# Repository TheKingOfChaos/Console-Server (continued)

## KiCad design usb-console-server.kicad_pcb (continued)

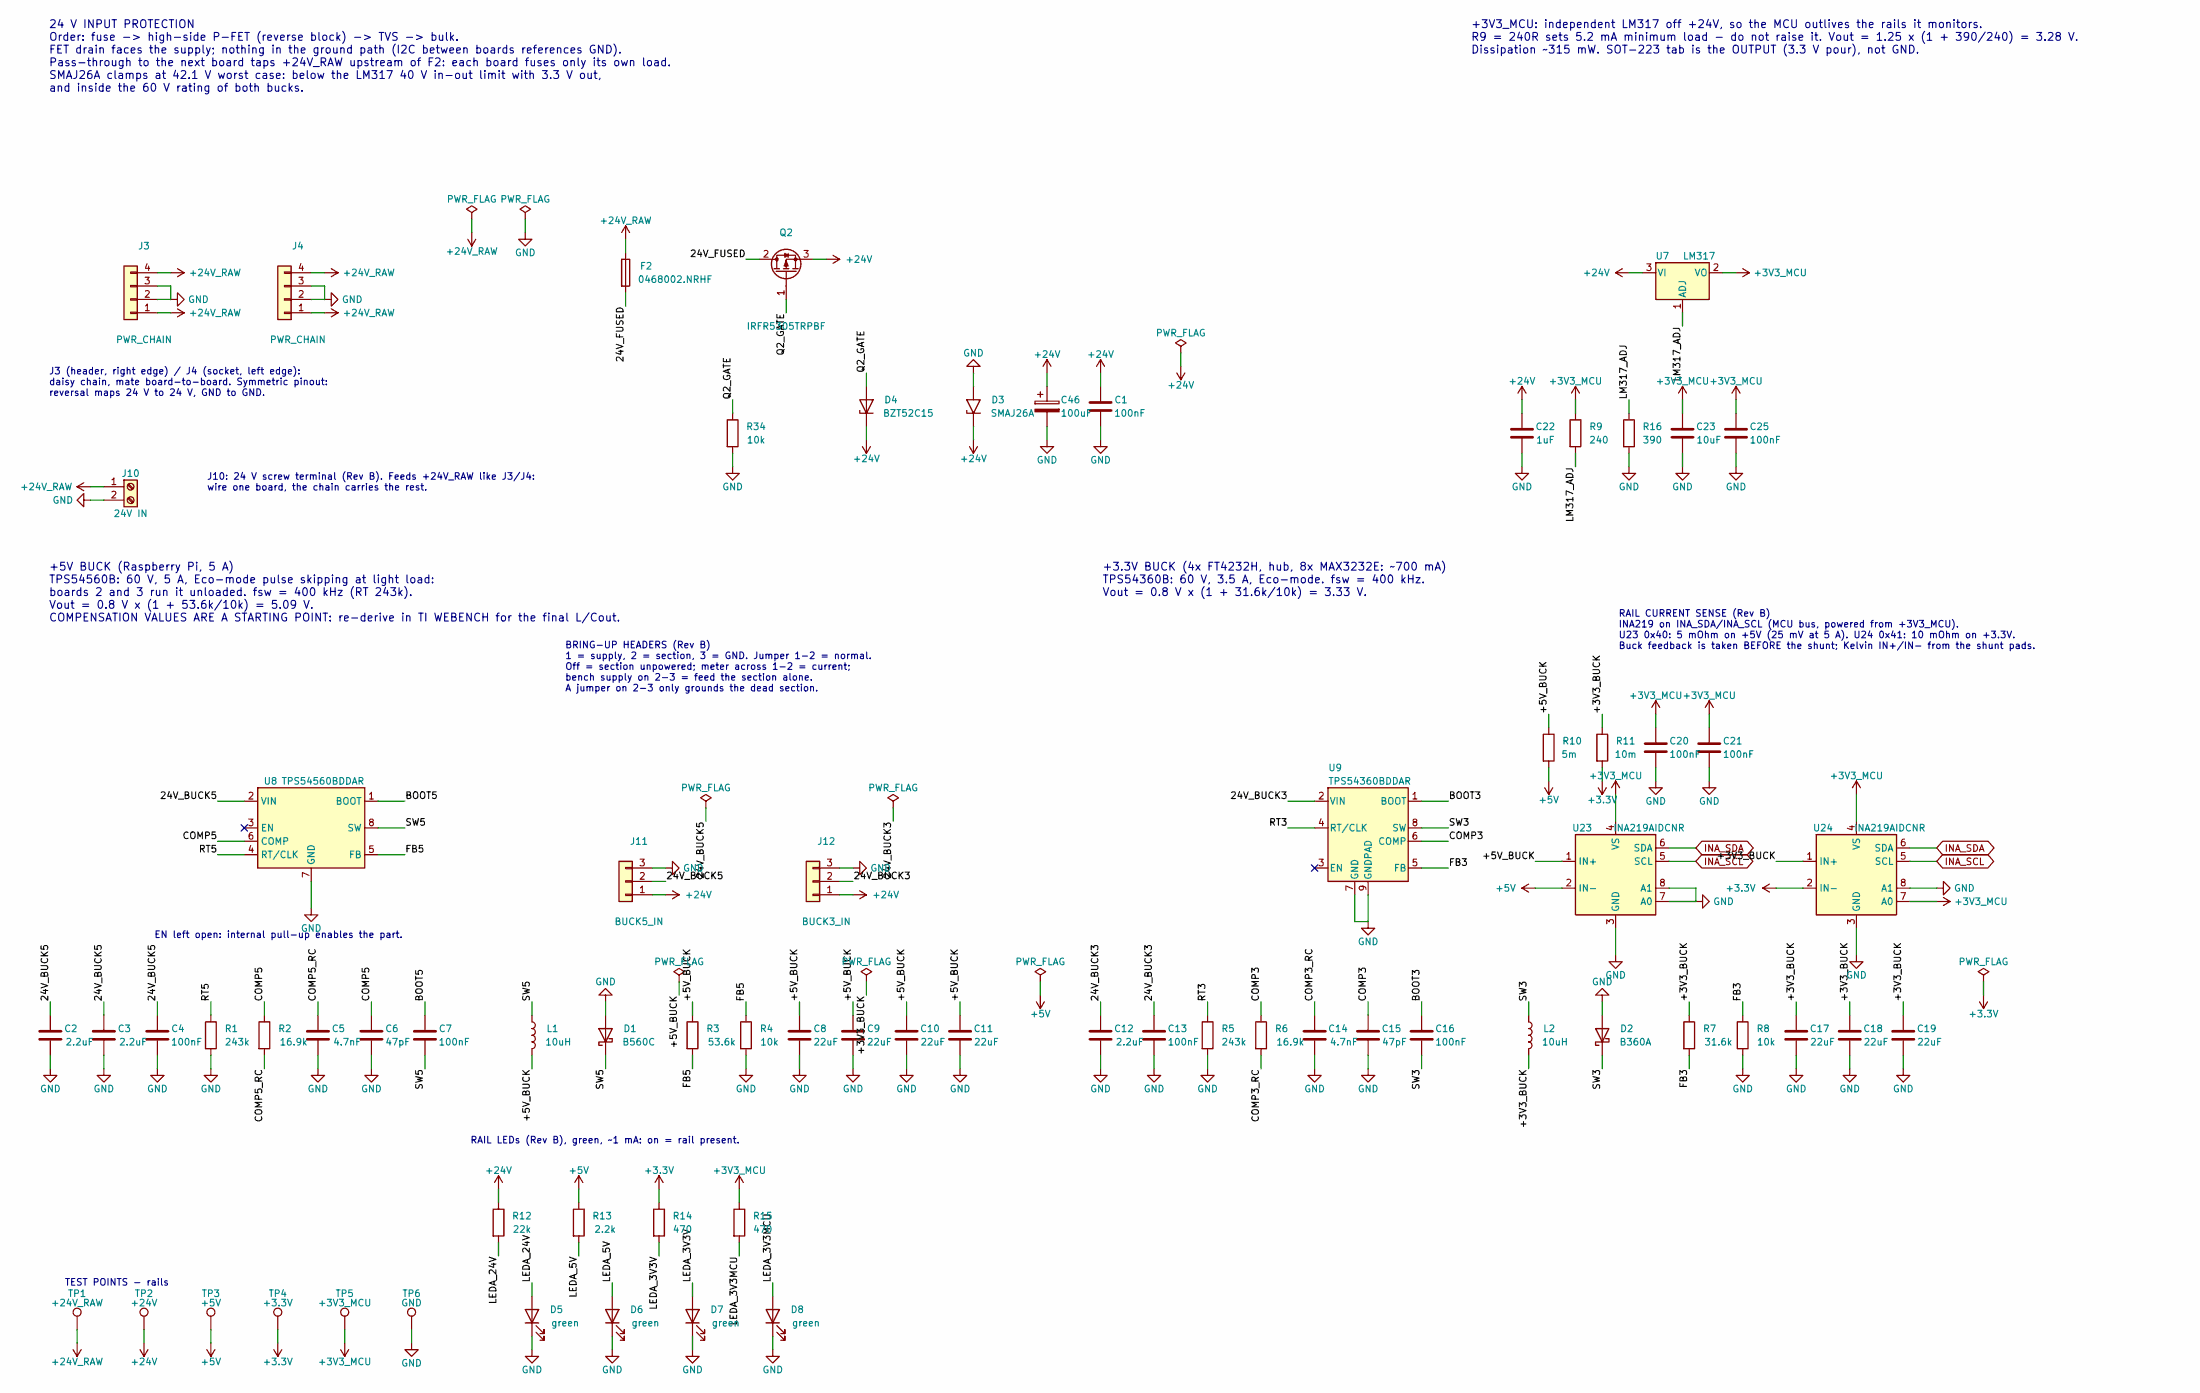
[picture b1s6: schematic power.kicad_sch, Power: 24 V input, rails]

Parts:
C1, C4, C7, C13, C16, C20, C21, C25: 100nF; C_0603_1608Metric; LCSC C14663
C2, C3, C12: 2.2uF; C_1210_3225Metric; LCSC C153036
C5, C14: 4.7nF; C_0603_1608Metric; LCSC C53987
C6, C15: 47pF; C_0603_1608Metric; LCSC C1671
C8, C9, C10, C11, C17, C18, C19: 22uF; C_1206_3216Metric; LCSC C77091
C22: 1uF; C_0805_2012Metric; LCSC C91185
C23: 10uF; C_0805_2012Metric; LCSC C15850
C46: 100uF; CP_Elec_10x10.5; LCSC C51953411
D1: B560C; D_SMC; LCSC C85100
D2: B360A; D_SMA; LCSC C94193
D3: SMAJ26A; D_SMA; LCSC C148225
D4: BZT52C15; D_SOD-123; LCSC C668893
D5, D6, D7, D8: green; LED_0603_1608Metric; LCSC C965805
F2: 0468002.NRHF; Fuse_1206_3216Metric; LCSC C187611
J3: PWR_CHAIN; PinHeader_1x04_P2.54mm_Horizontal; LCSC C492412
J4: PWR_CHAIN; PinSocket_1x04_P2.54mm_Horizontal; LCSC C2897386
J10: 24V IN; TerminalBlock_Phoenix_MKDS-1,5-2-5.08_1x02_P5.08mm_Horizont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; LCSC C8465
J11: BUCK5_IN; PinHeader_1x03_P2.54mm_Vertical; LCSC C49257
J12: BUCK3_IN; PinHeader_1x03_P2.54mm_Vertical; LCSC C49257
L1: 10uH; L_Bourns_SRP1265A; MPN TMPC1265HP-100MG-D; LCSC C305223
L2: 10uH; L_Bourns_SRP7028A_7.3x6.6mm; MPN SRP7028A-100M; LCSC C2687402
Q2: IRFR5305TRPBF; TO-252-3_L6.5-W6.1-P4.58-LS9.9-BR; LCSC C2624
R1, R5: 243k; R_0603_1608Metric; LCSC C403098
R2, R6: 16.9k; R_0603_1608Metric; LCSC C2933158
R3: 53.6k; R_0603_1608Metric; LCSC C2930115
R4, R8, R34: 10k; R_0603_1608Metric; LCSC C25804
R7: 31.6k; R_0603_1608Metric; LCSC C25967
R9: 240; R_0603_1608Metric; LCSC C114613
R10: 5m; R_2512_6332Metric; LCSC C393074
R11: 10m; R_1206_3216Metric; LCSC C188070
R12: 22k; R_0603_1608Metric; LCSC C31850
R13: 2.2k; R_0603_1608Metric; LCSC C4190
R14, R15: 470; R_0603_1608Metric; LCSC C23179
R16: 390; R_0603_1608Metric; LCSC C23151
TP1: +24V_RAW; TestPoint_Pad_D1.5mm
TP2: +24V; TestPoint_Pad_D1.5mm
TP3: +5V; TestPoint_Pad_D1.5mm
TP4: +3.3V; TestPoint_Pad_D1.5mm
TP5: +3V3_MCU; TestPoint_Pad_D1.5mm
TP6: GND; TestPoint_Pad_D1.5mm
U7: LM317; SOT-223-3_TabPin2; LCSC C5296732
U8: TPS54560BDDAR; Texas_HSOP-8-1EP_3.9x4.9mm_P1.27mm_ThermalVias; LCSC C1850354
U9: TPS54360BDDAR; TI_SO-PowerPAD-8_ThermalVias; LCSC C524806
U23, U24: INA219AIDCNR; SOT-23-8; LCSC C87469

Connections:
+3.3V: R11.2, R14.1, TP4.1, U24.2 (IN-); also elsewhere on the board
+3V3_MCU: C20.1, C21.1, C23.1, C25.1, R9.1, R15.1, TP5.1, U7.2 (VO), U23.4 (VS), U24.4 (VS), U24.7 (A0); also elsewhere on the board
+5V: R10.2, R13.1, TP3.1, U23.2 (IN-); also elsewhere on the board
+24V: C1.1, C22.1, C46.1, D3.1 (A1), D4.1 (K), J11.1, J12.1, Q2.3 (S), R12.1, TP2.1, U7.3 (VI); also elsewhere on the board
+24V_RAW: F2.1, J3.1, J3.4, J4.1, J4.4, J10.1, TP1.1
/Power/24V_BUCK3: C12.1, C13.1, J12.2, U9.2 (VIN)
/Power/24V_BUCK5: C2.1, C3.1, C4.1, J11.2, U8.2 (VIN)
/Power/24V_FUSED: F2.2, Q2.2 (D)
/Power/+3V3_BUCK: C17.1, C18.1, C19.1, L2.2, R7.1, R11.1, U24.1 (IN+)
/Power/+5V_BUCK: C8.1, C9.1, C10.1, C11.1, L1.2, R3.1, R10.1, U23.1 (IN+)
/Power/BOOT3: C16.1, U9.1 (BOOT)
/Power/BOOT5: C7.1, U8.1 (BOOT)
/Power/COMP3: C15.1, R6.1, U9.6 (COMP)
/Power/COMP3_RC: C14.1, R6.2
/Power/COMP5: C6.1, R2.1, U8.6 (COMP)
/Power/COMP5_RC: C5.1, R2.2
/Power/FB3: R7.2, R8.1, U9.5 (FB)
/Power/FB5: R3.2, R4.1, U8.5 (FB)
/Power/LEDA_3V3MCU: D8.2 (A), R15.2
/Power/LEDA_3V3V: D7.2 (A), R14.2
/Power/LEDA_5V: D6.2 (A), R13.2
/Power/LEDA_24V: D5.2 (A), R12.2
/Power/LM317_ADJ: R9.2, R16.1, U7.1 (ADJ)
/Power/Q2_GATE: D4.2 (A), Q2.1 (G), R34.1
/Power/RT3: R5.1, U9.4 (RT/CLK)
/Power/RT5: R1.1, U8.4 (RT/CLK)
/Power/SW3: C16.2, D2.1 (K), L2.1, U9.8 (SW)
/Power/SW5: C7.2, D1.1 (K), L1.1, U8.8 (SW)
GND: C1.2, C2.2, C3.2, C4.2, C5.2, C6.2, C8.2, C9.2, C10.2, C11.2, C12.2, C13.2, C14.2, C15.2, C17.2, C18.2, C19.2, C20.2, C21.2, C22.2, C23.2, C25.2, C46.2, D1.2 (A), D2.2 (A), D3.2 (A2), D5.1 (K), D6.1 (K), D7.1 (K), D8.1 (K), J3.2, J3.3, J4.2, J4.3, J10.2, J11.3, J12.3, R1.2, R4.2, R5.2, R8.2, R16.2, R34.2, TP6.1, U8.7 (GND), U8.9 (GND), U9.7 (GND), U9.9 (GNDPAD), U23.3 (GND), U23.7 (A0), U23.8 (A1), U24.3 (GND), U24.8 (A1); also elsewhere on the board
INA_SCL: U23.5 (SCL), U24.5 (SCL); also elsewhere on the board
INA_SDA: U23.6 (SDA), U24.6 (SDA); also elsewhere on the board

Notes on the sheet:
TEST POINTS - rails
RAIL LEDs (Rev B), green, ~1 mA: on = rail present.
24 V INPUT PROTECTION Order: fuse -> high-side P-FET (reverse block) -> TVS -> bulk. FET drain faces the supply; nothing in the ground path (I2C between boards references GND). Pass-through to the next board taps +24V_RAW upstream of F2: each board fuses only its own load. SMAJ26A clamps at 42.1 V 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
EN left open: internal pull-up enables the part.
J10: 24 V screw terminal (Rev B). Feeds +24V_RAW like J3/J4: wire one board, the chain carries the rest.
RAIL CURRENT SENSE (Rev B) INA219 on INA_SDA/INA_SCL (MCU bus, powered from +3V3_MCU). U23 0x40: 5 mOhm on +5V (25 mV at 5 A). U24 0x41: 10 mOhm on +3.3V. Buck feedback is taken BEFORE the shunt; Kelvin IN+/IN- from the shunt pads.
J3 (header, right edge) / J4 (socket, left edge): daisy chain, mate board-to-board. Symmetric pinout: reversal maps 24 V to 24 V, GND to GND.
BRING-UP HEADERS (Rev B) 1 = supply, 2 = section, 3 = GND. Jumper 1-2 = normal. Off = section unpowered; meter across 1-2 = current; bench supply on 2-3 = feed the section alone. A jumper on 2-3 only grounds the dead section.
+3.3V BUCK (4x FT4232H, hub, 8x MAX3232E: ~700 mA) TPS54360B: 60 V, 3.5 A, Eco-mode. fsw = 400 kHz. Vout = 0.8 V x (1 + 31.6k/10k) = 3.33 V.
+3V3_MCU: independent LM317 off +24V, so the MCU outlives the rails it monitors. R9 = 240R sets 5.2 mA minimum load - do not raise it. Vout = 1.25 x (1 + 390/240) = 3.28 V. Dissipation ~315 mW. SOT-223 tab is the OUTPUT (3.3 V pour), not GND.
+5V BUCK (Raspberry Pi, 5 A) TPS54560B: 60 V, 5 A, Eco-mode pulse skipping at light load: boards 2 and 3 run it unloaded. fsw = 400 kHz (RT 243k). Vout = 0.8 V x (1 + 53.6k/10k) = 5.09 V. COMPENSATION VALUES ARE A STARTING POINT: re-derive in TI WEBENCH for the final L/Cout.

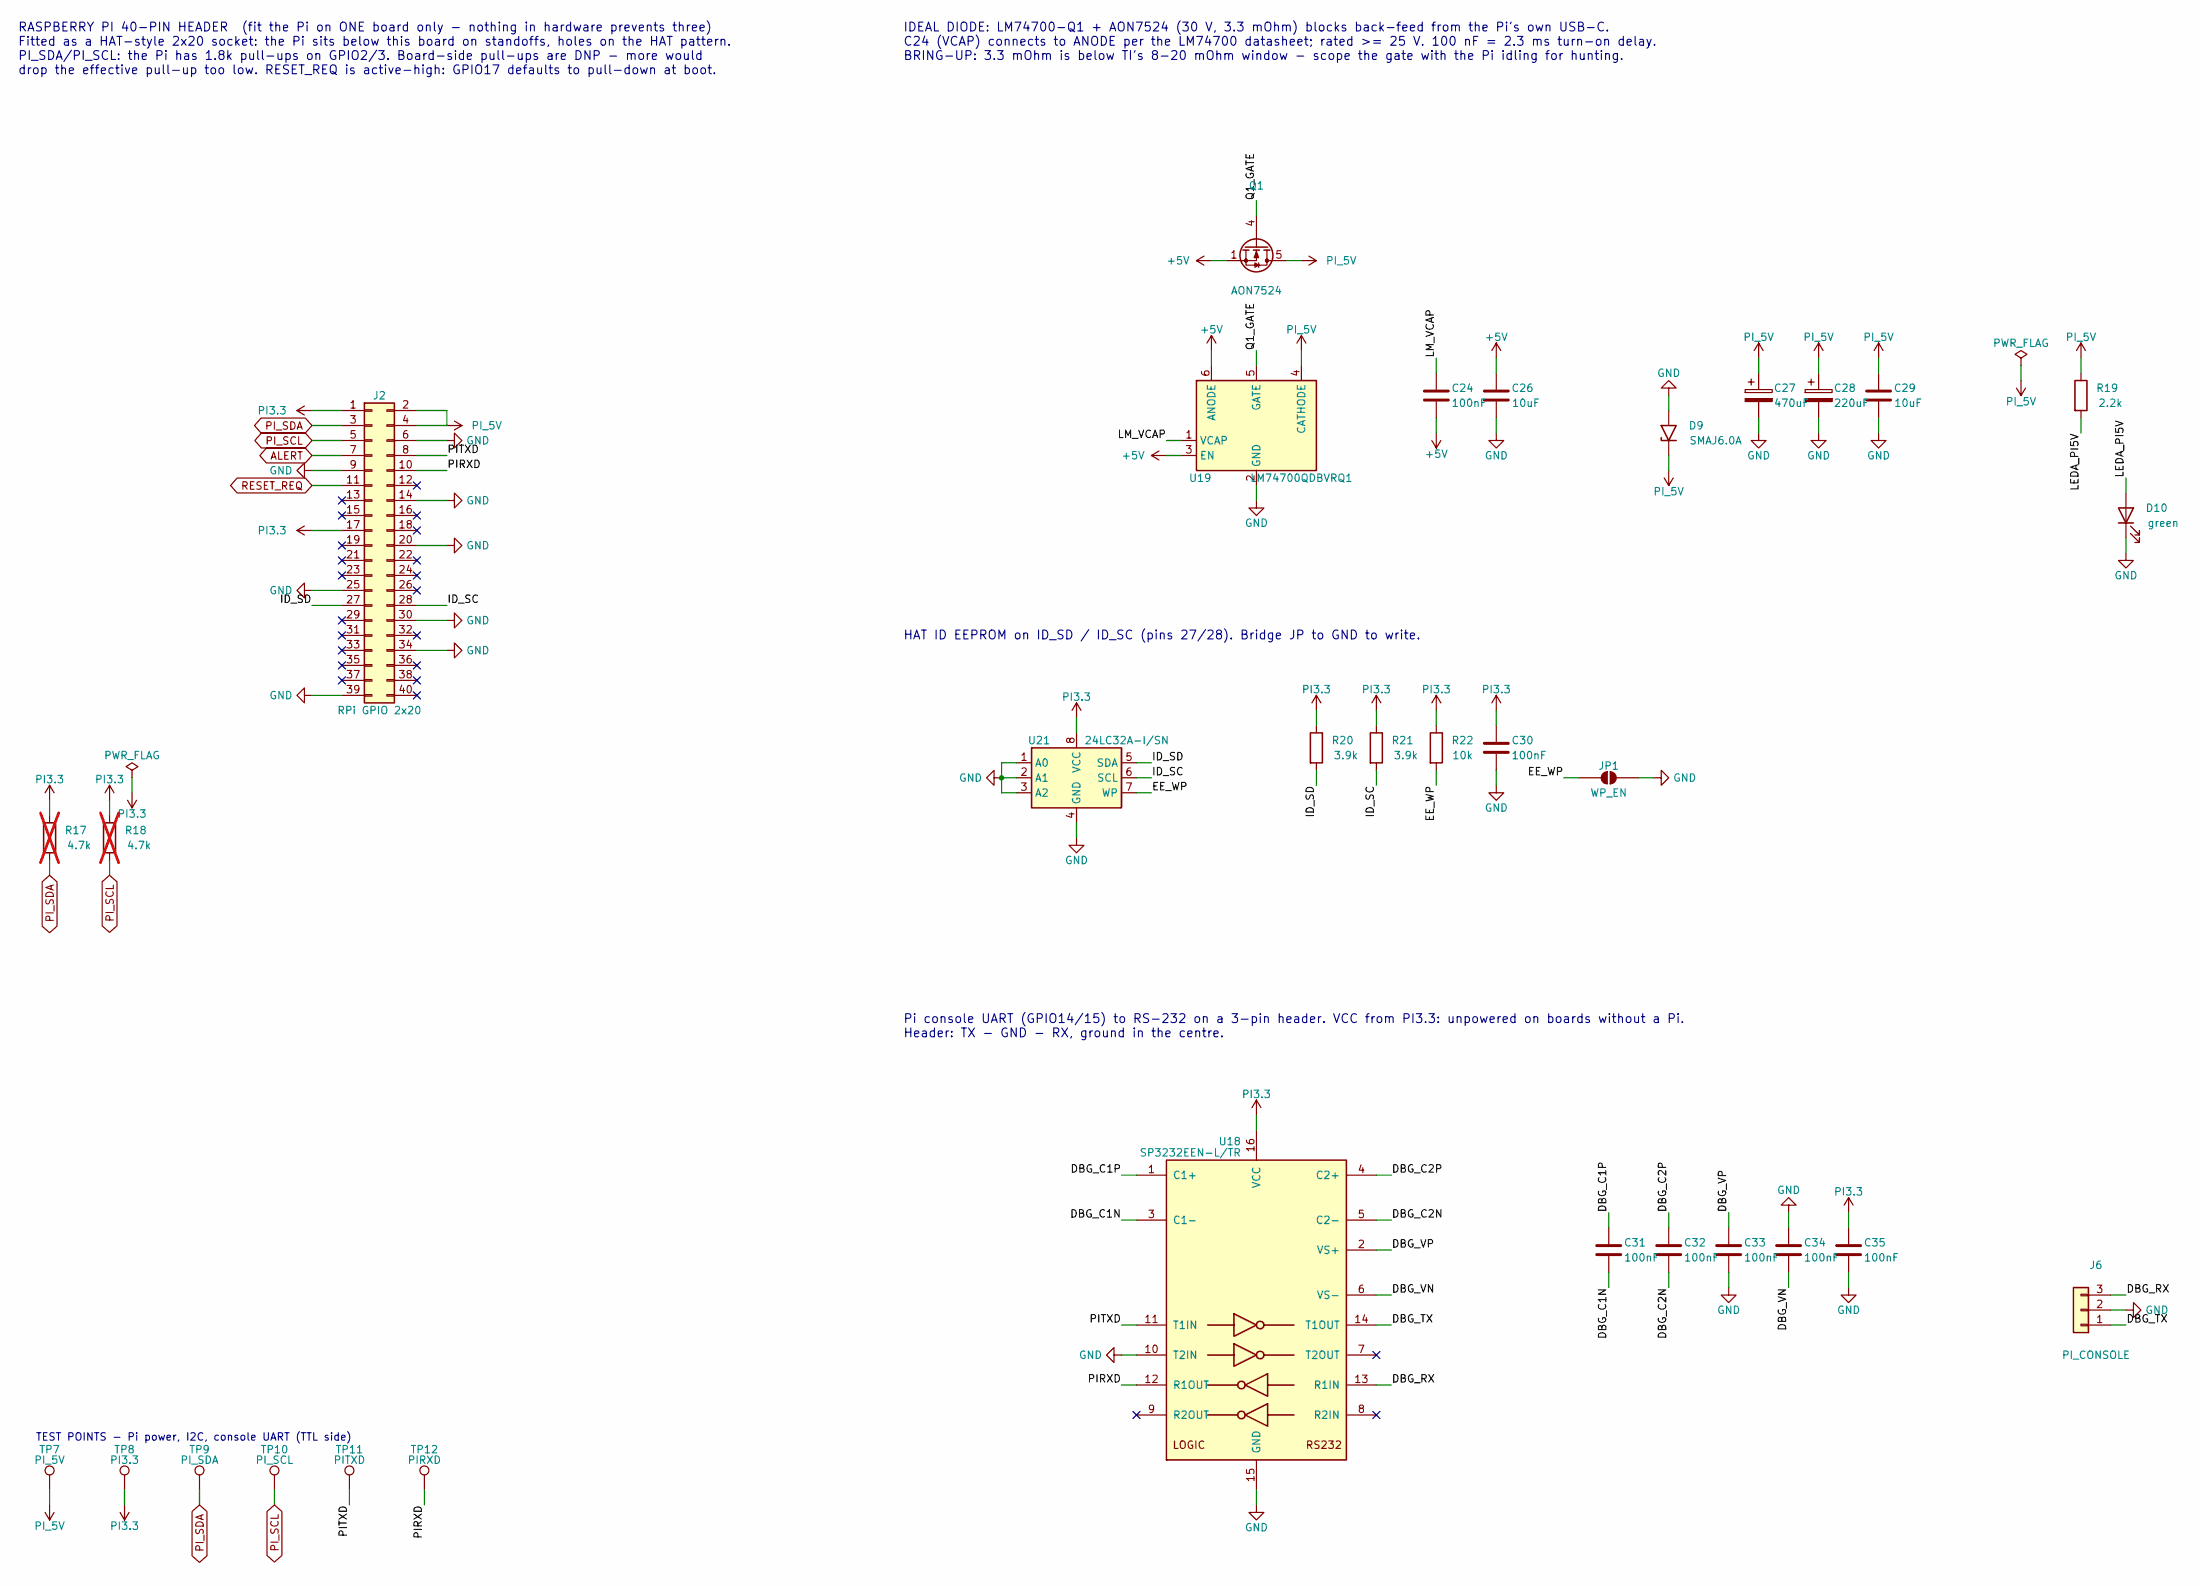
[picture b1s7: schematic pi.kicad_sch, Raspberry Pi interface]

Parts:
C24, C30, C31, C32, C33, C34, C35: 100nF; C_0603_1608Metric; LCSC C14663
C26, C29: 10uF; C_0805_2012Metric; LCSC C15850
C27: 470uF; CP_Elec_6.3x7.7; LCSC C335982
C28: 220uF; CP_Elec_6.3x5.4; LCSC C72494
D9: SMAJ6.0A; D_SMA; LCSC C223993
D10: green; LED_0603_1608Metric; LCSC C965805
J2: RPi GPIO 2x20; PinSocket_2x20_P2.54mm_Vertical; LCSC C2977589
J6: PI_CONSOLE; PinHeader_1x03_P2.54mm_Vertical; LCSC C49257
JP1: WP_EN; SolderJumper-2_P1.3mm_Open_RoundedPad1.0x1.5mm
Q1: AON7524; DFN-8_L3.0-W3.0-P0.65-BL-2; LCSC C431195
R17, R18: 4.7k; R_0603_1608Metric; LCSC C23162; not fitted
R19: 2.2k; R_0603_1608Metric; LCSC C4190
R20, R21: 3.9k; R_0603_1608Metric; LCSC C23018
R22: 10k; R_0603_1608Metric; LCSC C25804
TP7: PI_5V; TestPoint_Pad_D1.5mm
TP8: PI3.3; TestPoint_Pad_D1.5mm
TP9: PI_SDA; TestPoint_Pad_D1.0mm
TP10: PI_SCL; TestPoint_Pad_D1.0mm
TP11: PITXD; TestPoint_Pad_D1.0mm
TP12: PIRXD; TestPoint_Pad_D1.0mm
U18: SP3232EEN-L/TR; SOIC-16_3.9x9.9mm_P1.27mm; LCSC C9378
U19: LM74700QDBVRQ1; SOT-23-6; LCSC C2941042
U21: 24LC32A-I/SN; SOIC-8_3.9x4.9mm_P1.27mm; LCSC C511262

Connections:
+5V: C24.2, C26.1, Q1.1 (S), Q1.2 (S), Q1.3 (S), U19.3 (EN), U19.6 (ANODE); also elsewhere on the board
/Pi/DBG_C1N: C31.2, U18.3 (C1-)
/Pi/DBG_C1P: C31.1, U18.1 (C1+)
/Pi/DBG_C2N: C32.2, U18.5 (C2-)
/Pi/DBG_C2P: C32.1, U18.4 (C2+)
/Pi/DBG_RX: J6.3, U18.13 (R1IN)
/Pi/DBG_TX: J6.1, U18.14 (T1OUT)
/Pi/DBG_VN: C34.2, U18.6 (VS-)
/Pi/DBG_VP: C33.1, U18.2 (VS+)
/Pi/EE_WP: JP1.1 (A), R22.2, U21.7 (WP)
/Pi/ID_SC: J2.28, R21.2, U21.6 (SCL)
/Pi/ID_SD: J2.27, R20.2, U21.5 (SDA)
/Pi/LEDA_PI5V: D10.2 (A), R19.2
/Pi/LM_VCAP: C24.1, U19.1 (VCAP)
/Pi/PIRXD: J2.10, TP12.1, U18.12 (R1OUT)
/Pi/PITXD: J2.8, TP11.1, U18.11 (T1IN)
/Pi/Q1_GATE: Q1.4 (G), U19.5 (GATE)
ALERT: J2.7; also elsewhere on the board
GND: C26.2, C27.2, C28.2, C29.2, C30.2, C33.2, C34.1, C35.2, D9.2 (A2), D10.1 (K), J2.6, J2.9, J2.14, J2.20, J2.25, J2.30, J2.34, J2.39, J6.2, JP1.2 (B), U18.10 (T2IN), U18.15 (GND), U19.2 (GND), U21.1 (A0), U21.2 (A1), U21.3 (A2), U21.4 (GND); also elsewhere on the board
PI3.3: C30.1, C35.1, J2.1, J2.17, R17.1, R18.1, R20.1, R21.1, R22.1, TP8.1, U18.16 (VCC), U21.8 (VCC); also elsewhere on the board
PI_5V: C27.1, C28.1, C29.1, D9.1 (A1), J2.2, J2.4, Q1.5 (D), Q1.6 (D), Q1.7 (D), Q1.8 (D), Q1.9 (D), R19.1, TP7.1, U19.4 (CATHODE)
PI_SCL: J2.5, R18.2, TP10.1; also elsewhere on the board
PI_SDA: J2.3, R17.2, TP9.1; also elsewhere on the board
RESET_REQ: J2.11; also elsewhere on the board

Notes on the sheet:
Pi console UART (GPIO14/15) to RS-232 on a 3-pin header. VCC from PI3.3: unpowered on boards without a Pi. Header: TX - GND - RX, ground in the centre.
IDEAL DIODE: LM74700-Q1 + AON7524 (30 V, 3.3 mOhm) blocks back-feed from the Pi's own USB-C. C24 (VCAP) connects to ANODE per the LM74700 datasheet; rated >= 25 V. 100 nF = 2.3 ms turn-on delay. BRING-UP: 3.3 mOhm is below TI's 8-20 mOhm window - scope the gate with the Pi idling for hunting.
RASPBERRY PI 40-PIN HEADER (fit the Pi on ONE board only - nothing in hardware prevents three) Fitted as a HAT-style 2x20 socket: the Pi sits below this board on standoffs, holes on the HAT pattern. PI_SDA/PI_SCL: the Pi has 1.8k pull-ups on GPIO2/3. Board-side pull-ups are DNP - more would drop th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
TEST POINTS - Pi power, I2C, console UART (TTL side)
HAT ID EEPROM on ID_SD / ID_SC (pins 27/28). Bridge JP to GND to write.

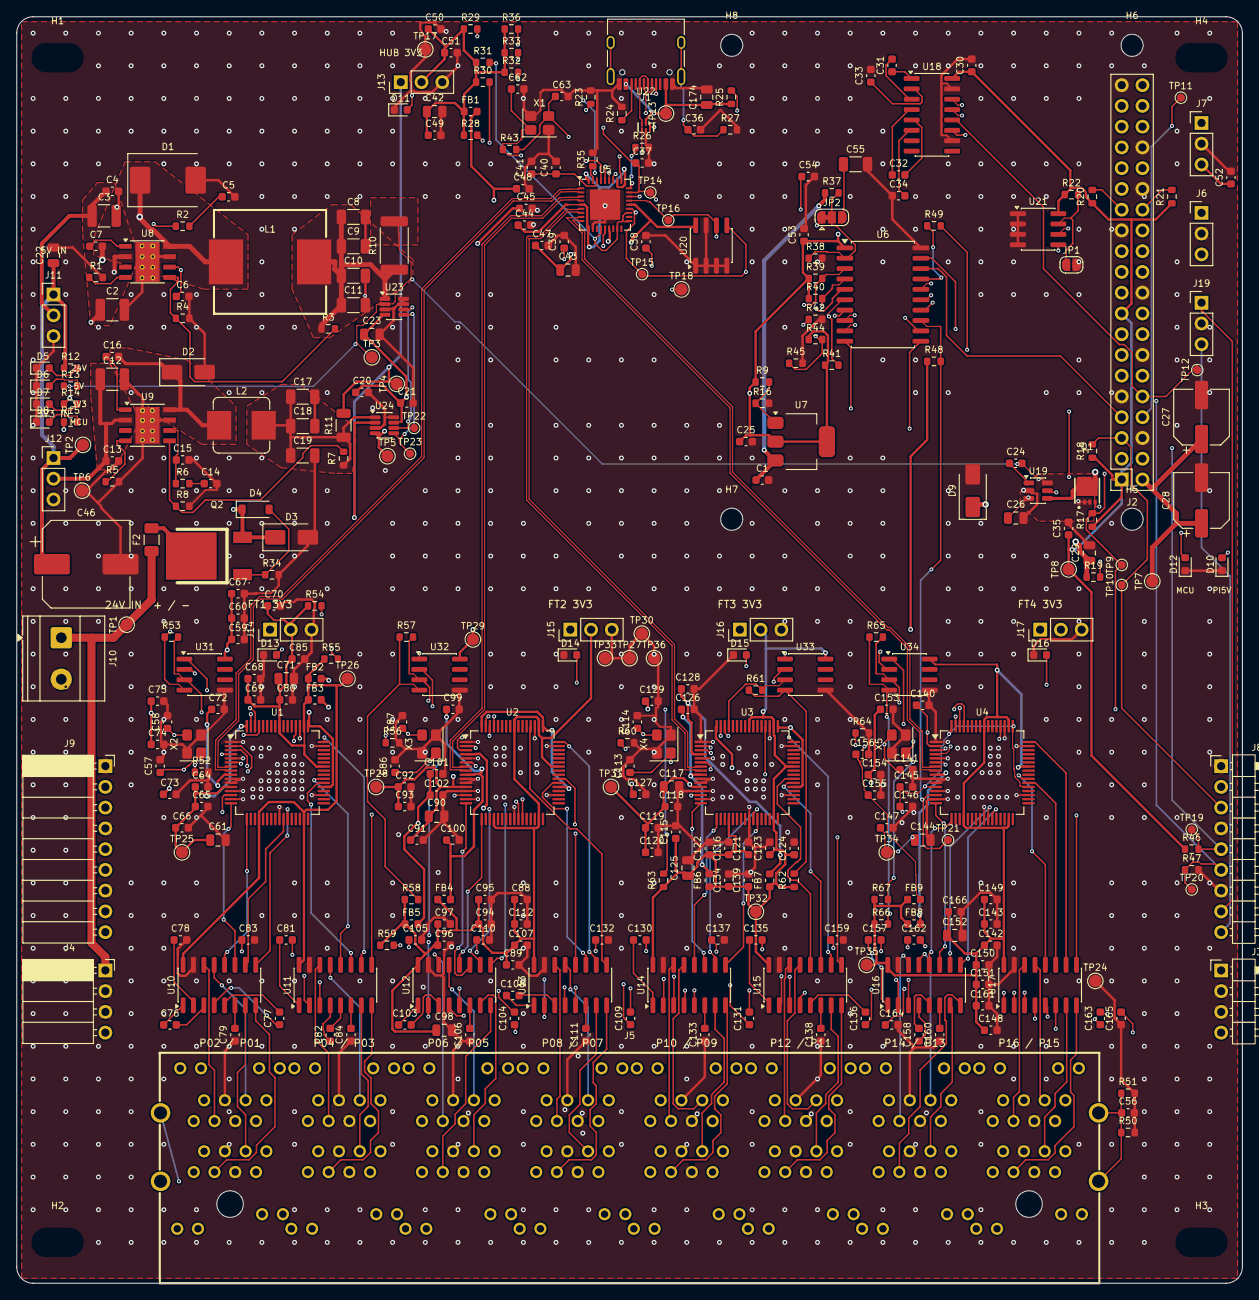
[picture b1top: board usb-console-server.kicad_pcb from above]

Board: 4 copper layers, 150.0 x 155.0 mm, 361 parts (0 on the bottom side), 255 nets.

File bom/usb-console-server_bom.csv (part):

"Designator","Value","Footprint","LCSC","Spec","MPN","Note","Qty","DNP"
"C1,C4,C7,C13,C16,C20,C21,C24,C25,C30,C31,C32,C33,C34,C35,C37,C39,C41,C44,C45,C47,C48,C49,C50,C51,C52,C54,C59,C60,C64,C65,C66,C67,C68,C69,C70,C72,C74,C76,C77,C78,C79,C80,C81,C82,C83,C84,C85,C88,C89,C91,C92,C93,C94,C95,C96,C97,C99,C101,C103,C104,C105,C106,C107,C108,C109,C110,C111,C112,C115,C116,C118,C119,C120,C121,C122,C123,C124,C126,C128,C130,C131,C132,C133,C134,C135,C136,C137,C138,C139,C142,C143,C145,C146,C147,C148,C149,C150,C151,C153,C155,C157,C158,C159,C160,C161,C162,C163,C164,C165,C166","100nF","Capacitor_SMD:C_0603_1608Metric","C14663","50V X7R","","VCAP to ANODE, >=25 V,VCCIO pin,VCORE pin,VREGIN","111",""
"C2,C3,C12","2.2uF","Capacitor_SMD:C_1210_3225Metric","C153036","100V X7R","","","3",""
"C5,C14,C36","4.7nF","Capacitor_SMD:C_0603_1608Metric","C53987","50V X7R","","","3",""
"C6,C15","47pF","Capacitor_SMD:C_0603_1608Metric","C1671","50V C0G","","","2",""
"C8,C9,C10,C11,C17,C18,C19,C55","22uF","Capacitor_SMD:C_1206_3216Metric","C77091","25V X5R","","","8",""
"C22,C174","1uF","Capacitor_SMD:C_0805_2012Metric","C91185","50V X7R","","","2",""
"C23,C26,C29,C71,C98,C125,C152","10uF","Capacitor_SMD:C_0805_2012Metric","C15850","25V X5R","","local bulk","7",""
"C27","470uF","Capacitor_SMD:CP_Elec_6.3x7.7","C335982","10V electrolytic 6.3x7.7","","","1",""
"C28","220uF","Capacitor_SMD:CP_Elec_6.3x5.4","C72494","10V electrolytic 6.3x5.4","","","1",""
"C38,C40,C53,C73,C75,C100,C102,C127,C129,C154,C156","1uF","Capacitor_SMD:C_0603_1608Metric","C29936","25V X7R","","","11",""
"C42,C43,C61,C90,C117,C144","4.7uF","Capacitor_SMD:C_0805_2012Metric","C1779","25V X5R","","VREGOUT: LDO compensation, min 3.3 uF","6",""
"C46","100uF","Capacitor_SMD:CP_Elec_10x10.5","C51953411","63V electrolytic 10x10.5","","","1",""
"C57,C58,C86,C87,C113,C114,C140,C141","33pF","Capacitor_SMD:C_0603_1608Metric","C1663","50V C0G","","C0G","8",""
"C62,C63","15pF","Capacitor_SMD:C_0603_1608Metric","C1644","50V C0G","","C0G, matched to 12 pF CL","2",""
"D1","B560C","Diode_SMD:D_SMC","C85100","","","","1",""
"D2","B360A","Diode_SMD:D_SMA","C94193","","","","1",""
"D3","SMAJ26A","Diode_SMD:D_SMA","C148225","","","26 V standoff, 42.1 V max clamp","1",""
"D4","BZT52C15","Diode_SMD:D_SOD-123","C668893","","","15 V gate clamp, cathode to source","1",""
"D5,D6,D7,D8,D10,D11,D12,D13,D14,D15,D16","green","LED_SMD:LED_0603_1608Metric","C965805","","","+24V present,+3.3V present,+3V3_MCU present,+5V present,Pi 5 V present,cluster powered,heartbeat = healthy; solid or dark = hung,hub section powered","11",""
"D9","SMAJ6.0A","Diode_SMD:D_SMA","C223993","","","","1",""
"F2","0468002.NRHF","Fuse:Fuse_1206_3216Metric","C187611","","","2 A time-lag 63 V DC, I2t 0.506 A2s","1",""
"FB1,FB2,FB3,FB4,FB5,FB6,FB7,FB8,FB9","BLM18KG601SN1D","Inductor_SMD:L_0603_1608Metric","C85833","","","","9",""
"J1","USB-C","Connector_USB:USB_C_Receptacle_HRO_TYPE-C-31-M-12","C165948","","","","1",""
"J2","RPi GPIO 2x20","Connector_PinSocket_2.54mm:PinSocket_2x20_P2.54mm_Vertical","C2977589","","","","1",""
"J3","PWR_CHAIN","Connector_PinHeader_2.54mm:PinHeader_1x04_P2.54mm_Horizontal","C492412","","","1x04 R/A pin header","1",""
"J4","PWR_CHAIN","Connector_PinSocket_2.54mm:PinSocket_1x04_P2.54mm_Horizontal","C2897386","","","1x04 R/A socket","1",""
"J5","HC-RJ45-059D-2x8-2-04","console_server:RJ45_HC-RJ45-059D-2x8","C46261623","","","","1",""
"J6","PI_CONSOLE","Connector_PinHeader_2.54mm:PinHeader_1x03_P2.54mm_Vertical","C49257","","","","1",""
"J7","UPDI","Connector_PinHeader_2.54mm:PinHeader_1x03_P2.54mm_Vertical","C49257","","","","1",""
"J8","LINK","Connector_PinHeader_2.54mm:PinHeader_1x09_P2.54mm_Horizontal","C492417","","","","1",""
"J9","LINK","Connector_PinSocket_2.54mm:PinSocket_1x09_P2.54mm_Horizontal","C2897391","","","","1",""
"J10","24V IN","TerminalBlock_Phoenix:TerminalBlock_Phoenix_MKDS-1,5-2-5.08_1x02_P5.08mm_Horizontal","C8465","","","5.08 mm screw terminal, 18 A; same node as the chain connectors","1",""
"J11","BUCK5_IN","Connector_PinHeader_2.54mm:PinHeader_1x03_P2.54mm_Vertical","C49257","","","bring-up jumper, 1.2 A max","1",""
"J12","BUCK3_IN","Connector_PinHeader_2.54mm:PinHeader_1x03_P2.54mm_Vertical","C49257","","","bring-up jumper, 1.2 A max","1",""
"J13","HUB_3V3","Connector_PinHeader_2.54mm:PinHeader_1x03_P2.54mm_Vertical","C49257","","","bring-up jumper","1",""
"J14,J15,J16,J17","FT_3V3","Connector_PinHeader_2.54mm:PinHeader_1x03_P2.54mm_Vertical","C49257","","","bring-up jumper","4",""
"J19","MCU_UART","Connector_PinHeader_2.54mm:PinHeader_1x03_P2.54mm_Vertical","C49257","","","","1",""
"L1","10uH","console_server:L_Bourns_SRP1265A","C305223","","TMPC1265HP-100MG-D","Isat 15.5 A, Irms 10 A (SRP1265A-100M equivalent)","1",""
"L2","10uH","Inductor_SMD:L_Bourns_SRP7028A_7.3x6.6mm","C2687402","","SRP7028A-100M","Isat 6 A, Irms 3.5 A","1",""
"Q1","AON7524","console_server:DFN-8_L3.0-W3.0-P0.65-BL-2","C431195","","","","1",""
"Q2","IRFR5305TRPBF","console_server:TO-252-3_L6.5-W6.1-P4.58-LS9.9-BR","C2624","","","P-ch 55 V 65 mOhm; drain to input","1",""
"R1,R5","243k","Resistor_SMD:R_0603_1608Metric","C403098","1% 0603","","","2",""
"R2,R6","16.9k","Resistor_SMD:R_0603_1608Metric","C2933158","1% 0603","","","2",""
"R3","53.6k","Resistor_SMD:R_0603_1608Metric","C2930115","1% 0603","","","1",""
"R4,R8,R22,R28,R29,R30,R31,R32,R33,R34,R41,R44,R46,R48,R54,R58,R62,R66","10k","Resistor_SMD:R_0603_1608Metric","C25804","1% 0603","","SCL pull-up AND CFG_SEL0 strap,one pull-up for all four FT4232H","18",""
"R7","31.6k","Resistor_SMD:R_0603_1608Metric","C25967","1% 0603","","","1",""
"R9","240","Resistor_SMD:R_0603_1608Metric","C114613","1% 0603","","1.25V/240R = 5.2 mA min load; do not raise","1",""
"R10","5m","Resistor_SMD:R_2512_6332Metric","C393074","5 mOhm 1% 3W 2512 shunt","","+5V shunt","1",""
"R11","10m","Resistor_SMD:R_1206_3216Metric","C188070","10 mOhm 1% 1W 1206 shunt","","+3.3V shunt","1",""
"R12","22k","Resistor_SMD:R_0603_1608Metric","C31850","1% 0603","","","1",""
"R13,R19,R53,R57,R61,R65","2.2k","Resistor_SMD:R_0603_1608Metric","C4190","1% 0603","","","6",""
"R14,R15,R36,R55,R59,R63,R67","470","Resistor_SMD:R_0603_1608Metric","C23179","1% 0603","","","7",""
"R16","390","Resistor_SMD:R_0603_1608Metric","C23151","1% 0603","","","1",""
"R20,R21","3.9k","Resistor_SMD:R_0603_1608Metric","C23018","1% 0603","","","2",""
"R23,R24","5.1k","Resistor_SMD:R_0603_1608Metric","C23186","1% 0603","","","2",""
"R25,R37","47k","Resistor_SMD:R_0603_1608Metric","C111134","1% 0603","","","2",""
"R26,R47","100k","Resistor_SMD:R_0603_1608Metric","C25803","1% 0603","","","2",""
"R27","1M","Resistor_SMD:R_0603_1608Metric","C22935","1% 0603","","","1",""
"R35,R52,R56,R60,R64","12k","Resistor_SMD:R_0603_1608Metric","C22790","1%","","","5",""
"R38","4.3k","Resistor_SMD:R_0603_1608Metric","C23159","1% 0603","","","1",""
"R39,R40","4.7k","Resistor_SMD:R_0603_1608Metric","C23162","1% 0603","","","2",""
"R42,R45,R50","0","Resistor_SMD:R_0603_1608Metric","C21189","jumper","","ID strap: fit on boards 1, 2,ID strap: fit on boards 1, 3","3",""
"R49","1k","Resistor_SMD:R_0603_1608Metric","C22548","1% 0603","","","1",""
"U1,U2,U3,U4","FT4232HL","Package_QFP:LQFP-64_10x10mm_P0.5mm","C56742","","","","4",""
"U5","USB2514BI-AEZG-TR","Package_DFN_QFN:QFN-36-1EP_6x6mm_P0.5mm_EP3.7x3.7mm","C58940","","","","1",""
"U6","ATtiny3216-SF","Package_SO:SOIC-20W_7.5x12.8mm_P1.27mm","C1340355","","","","1",""
"U7","LM317","Package_TO_SOT_SMD:SOT-223-3_TabPin2","C5296732","","","","1",""
"U8","TPS54560BDDAR","Package_SO:Texas_HSOP-8-1EP_3.9x4.9mm_P1.27mm_ThermalVias","C1850354","","","","1",""
"U9","TPS54360BDDAR","Package_SO:TI_SO-PowerPAD-8_ThermalVias","C524806","","","","1",""
"U10,U11,U12,U13,U14,U15,U16,U17","MAX3232EIDR","Package_SO:SOIC-16_3.9x9.9mm_P1.27mm","C193666","","","","8",""
"U18","SP3232EEN-L/TR","Package_SO:SOIC-16_3.9x9.9mm_P1.27mm","C9378","","","","1",""
"U19","LM74700QDBVRQ1","Package_TO_SOT_SMD:SOT-23-6","C2941042","","","","1",""
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
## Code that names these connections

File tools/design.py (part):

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pi = P.sheet('pi.kicad_sch', 'Raspberry Pi interface')
pi.text('RASPBERRY PI 40-PIN HEADER  (fit the Pi on ONE board only - nothing in hardware prevents three)\n'
        'Fitted as a HAT-style 2x20 socket: the Pi sits below this board on standoffs, holes on the HAT pattern.\n'
        'PI_SDA/PI_SCL: the Pi has 1.8k pull-ups on GPIO2/3. Board-side pull-ups are DNP - more would\n'
        'drop the effective pull-up too low. RESET_REQ is active-high: GPIO17 defaults to pull-down at boot.', (20, 22))
pi_nets = {str(n): None for n in range(1, 41)}
pi_nets.update({'1': 'PI3.3', '17': 'PI3.3', '2': 'PI_5V', '4': 'PI_5V', '3': 'PI_SDA', '5': 'PI_SCL', '7': 'ALERT',
                '8': 'PITXD', '10': 'PIRXD', '11': 'RESET_REQ', '27': 'ID_SD', '28': 'ID_SC'})
for g in (6, 9, 14, 20, 25, 30, 34, 39):
    pi_nets[str(g)] = 'GND'
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       fp='Connector_PinSocket_2.54mm:PinSocket_2x20_P2.54mm_Vertical', fields=flds('J:2x20_skt'), label_len=5.08)
flag(pi, 'PI3.3', 40, 150)
r = Row(pi, 25, 160)
r.R('4.7k', 'PI3.3', 'PI_SDA', dnp=True, extra={'Note': 'DNP - Pi has 1.8k on board'})
r.R('4.7k', 'PI3.3', 'PI_SCL', dnp=True, extra={'Note': 'DNP - Pi has 1.8k on board'})

# ideal diode
pi.text('IDEAL DIODE: LM74700-Q1 + AON7524 (30 V, 3.3 mOhm) blocks back-feed from the Pi\'s own USB-C.\n'
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       fields=flds('D:LED_G', Note='Pi 5 V present'))

# HAT ID EEPROM
pi.text('HAT ID EEPROM on ID_SD / ID_SC (pins 27/28). Bridge JP to GND to write.', (170, 125))
pi.add('Memory_EEPROM:24LC32', (200, 150), 'U21', '24LC32A-I/SN',
       {'1': 'GND', '2': 'GND', '3': 'GND', '4': 'GND', '5': 'ID_SD', '6': 'ID_SC', '7': 'EE_WP', '8': 'PI3.3'},
       fp='Package_SO:SOIC-8_3.9x4.9mm_P1.27mm', fields=flds('U:24LC32A'))
r = Row(pi, 240, 145)
r.R('3.9k', 'PI3.3', 'ID_SD')
r.R('3.9k', 'PI3.3', 'ID_SC')
r.R('10k', 'PI3.3', 'EE_WP')
r.C('100nF', 'PI3.3', 'GND')
pi.add('Jumper:SolderJumper_2_Open', (290, 150), 'JP', 'WP_EN', {'1': 'EE_WP', '2': 'GND'},
       fp='Jumper:SolderJumper-2_P1.3mm_Open_RoundedPad1.0x1.5mm', in_bom=False)
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ft = P.sheet('ftdi.kicad_sch', 'FT4232H cluster (x4): 4 UART channels -> 4 RS-232 ports')
ft.text('ONE OF FOUR IDENTICAL CLUSTERS. Compound device: no VBUS at the FTDI, no VBUS divider into RESET#.\n'
        'VREGOUT -> VCORE is an EXTERNAL connection (4.7 uF compensates the internal LDO).\n'
        'VPLL and VPHY are 3.3 V, each on its own ferrite. All four VCCIO pins must be connected.\n'
        'TEST hard to GND (floating = factory test mode, never enumerates). Channel D RXD is pin 52, not 49.\n'
        'Only TXD/RXD used per channel; modem pins have internal 40-190k pulls.', (20, 22))
ft_idx = lambda i: i  # noqa
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r.C('100nF', 'VCC3', 'GND', extra={'Note': 'VREGIN'})
r.C('4.7uF', 'VCORE', 'GND', key='C:4.7uF', fp=FP['C0805'], extra={'Note': 'VREGOUT: LDO compensation, min 3.3 uF'})
for _ in range(3):
    r.C('100nF', 'VCORE', 'GND', extra={'Note': 'VCORE pin'})
for _ in range(4):
    r.C('100nF', 'VCC3', 'GND', extra={'Note': 'VCCIO pin'})
r.C('10uF', 'VCC3', 'GND', key='C:10uF', fp=FP['C0805'], extra={'Note': 'local bulk'})
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           {str(24 * ((port - 1) // 2) + (0 if port % 2 else 8) + c): n for c, n in
            {1: None, 2: None, 3: f'P{port:02d}_RXD', 4: 'GND', 5: 'GND', 6: f'P{port:02d}_TXD', 7: None, 8: None}.items()},
           unit=port, fields=flds('J:RJ45x16'), label_len=5.08)
pt.add('console_server:HC-RJ45-059D-2x8', (60, 240), 'J5', 'HC-RJ45-059D-2x8-2-04', {'193': 'RJ_SHIELD'}, unit=17,
       fields=flds('J:RJ45x16'))
pt.text('SHIELD: all 16 shells common through the frame, one connection point.\n'
        'Footprint set 0R / high-value R / C - 0R fitted. Keeps the option to break the\n'
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mc = P.sheet('mcu.kicad_sch', 'Housekeeping MCU and inter-board link')
mc.text('ATtiny3216 at 10 MHz (internal 20 MHz / 2; 20 MHz needs 4.5 V). I2C target to the Pi at 0x30/0x31/0x32.\n'
        'Keep a pre-computed register snapshot so a read never stretches SCL (Broadcom BSC). 100 kHz.\n'
        'Tri-state PC2/PC3 (hub EEPROM bus) whenever +3.3V is down - the MCU outlives it by design.\n'
        'ALERT is open-drain in firmware; pull-up to PI3.3 so it exists only with a Pi (no back-power).\n'
        'Do not fuse PA0 to RESET: recovering UPDI needs a 12 V pulse.', (20, 22))
mc.add('MCU_Microchip_ATtiny:ATtiny3216-S', (90, 130), 'U6', 'ATtiny3216-SF',
       {'1': '+3V3_MCU', '2': 'SENSE_24V', '3': 'INA_SDA', '4': 'INA_SCL', '5': 'MCU_PA7', '6': 'ID1', '7': 'ID0',
        '8': 'SPARE2', '9': 'SPARE1', '10': 'PI_SDA', '11': 'PI_SCL', '12': 'HUB_MR_N', '13': 'FTDI_RST_N',
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r = Row(mc, 30, 185)
r.C('100nF', '+3V3_MCU', 'GND')
r.C('1uF', '+3V3_MCU', 'GND', key='C:1uF')
mc.add('Connector:TestPoint', (60, 175), 'TP', 'PA7', {'1': 'MCU_PA7'}, fp='TestPoint:TestPoint_Pad_D1.5mm',
       in_bom=False)
mc.add('Connector_Generic:Conn_01x03', (40, 75), 'J7', 'UPDI', {'1': 'UPDI', '2': 'GND', '3': '+3V3_MCU'},
       fp='Connector_PinHeader_2.54mm:PinHeader_1x03_P2.54mm_Vertical', fields=flds('J:1x03_hdr'), rot=180)
mc.text('UPDI: GND in the centre. A reversed plug swaps\n+3V3 and UPDI but never the reference.', (20, 85), 1.27)

mc.text('RAIL MONITORING: +24V on the ADC (~2.0 V at nominal vs internal 2.5 V ref). +5V and +3.3V voltage AND\n'
        'current come from the two INA219s (power sheet) on PA5/PA6 = INA_SDA/INA_SCL, bit-banged, own pull-ups.\n'
        'Senses protected +24V, not +24V_RAW. JP2 selects 100 nF (default) or 22 uF on the 24 V tap:\n'
        'SHIP ON 100 nF - 22 uF x 3.9k = 86 ms averages away the dip the monitor exists to catch.', (170, 22))
r = Row(mc, 175, 55)
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r.R('10k', '+3V3_MCU', 'ID0')
r.R('0', 'ID0', 'GND', key='R:0', extra={'Note': 'ID strap: fit on boards 1, 3'})
r.gap()
r.R('10k', 'PI3.3', 'ALERT')
r.R('100k', 'RESET_REQ', 'GND')
r.R('10k', '+3.3V', 'FTDI_RST_N', extra={'Note': 'one pull-up for all four FT4232H'})
r.gap()
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mc.add('Device:LED', (r.x + 5, 150), 'D', 'green', {'2': 'LED_A', '1': 'GND'}, rot=90, fp=FP['LED'],
       fields=flds('D:LED_G', Note='heartbeat = healthy; solid or dark = hung'))

mc.text('MCU UART (Rev B): J19 = TX (PB2) - GND - RX (PB3), USART0 default pins.\n'
        'Shared with SPARE1/SPARE2 on the link: debug one board at a time.', (20, 208), 1.27)
mc.add('Connector_Generic:Conn_01x03', (40, 228), 'J19', 'MCU_UART', {'1': 'SPARE1', '2': 'GND', '3': 'SPARE2'},
       fp='Connector_PinHeader_2.54mm:PinHeader_1x03_P2.54mm_Vertical', fields=flds('J:1x03_hdr'), rot=180)
mc.text('INTER-BOARD SIGNAL LINK, 9-way (power is a separate 4-way: different pin counts cannot be swapped).\n'
        'J8 header (right edge) mates J9 socket (left edge) of the next board directly - no cable.\n'
        'The invariant is physical position, not pin number. SPARE1/SPARE2 sit on USART0 (PB2/PB3) for an\n'
        'RS-485 migration if the single-ended link misbehaves. ~100 pF vs Pi 1.8k = ~150 ns rise (1 us limit).', (170, 190))
link = {'1': 'GND', '2': 'PI_SDA', '3': 'PI_SCL', '4': 'GND', '5': 'ALERT', '6': 'RESET_REQ', '7': 'GND',
        '8': 'SPARE1', '9': 'SPARE2'}
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
test_points(pw, 25, 270, [('+24V_RAW', True), ('+24V', True), ('+5V', True), ('+3.3V', True), ('+3V3_MCU', True),
                          ('GND', True)], 'TEST POINTS - rails')
test_points(pi, 25, 270, [('PI_5V', True), ('PI3.3', True), ('PI_SDA', False), ('PI_SCL', False), ('PITXD', False),
                          ('PIRXD', False)], 'TEST POINTS - Pi power, I2C, console UART (TTL side)')
test_points(hub, 25, 275, [('VBUS_UP', True), ('HUB_MR_N', False), ('HUB_SDA', False), ('HUB_SCL', False),
                           ('GND', True)], 'TEST POINTS - hub')
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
